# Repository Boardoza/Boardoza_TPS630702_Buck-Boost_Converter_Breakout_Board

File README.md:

# Boardoza TPS630702 Buck-Boost Regulator Module

The TPS630702 Buck-Boost Converter Breakout Board is an efficient, compact power management solution for applications requiring stable voltage output over a wide input voltage range. This module features automatic transition between step-down and boost mode, making it ideal for battery-powered projects. With high efficiency of up to 95%, adjustable output voltage selection, and multiple safety protections, it provides a reliable power supply for embedded systems, IoT devices, and other electronics requiring regulated power.

## [Click here to purchase!](https://www.ozdisan.com/maker-ve-iot-urunleri/boardoza/boardoza-modulleri/BOARDOZA-TPS630702/1206511)

|Front Side|Back Side|
|:---:|:---:|
| | |

---

## Key Features

- **Wide Input Voltage Range**: Operates from 2.0V to 16V, suitable for battery and adapter applications.
- **Selectable Output Voltage**: Provides 3.3V by default, with options for 5V, 7.5V, and 9V via jumper selection.
- **High Current Capability**: Supports up to **2A output in both Buck and Boost modes**.
- **Automatic Buck-Boost Transition**: Seamlessly switches between step-down and boost mode depending on input voltage.
- **Load Disconnect & Output Discharge**: Ensures safety during shutdown.
- **Efficiency**: Up to 95%, reducing heat dissipation and improving battery life.
- **Protection Features**: Includes input/output overvoltage protection and undervoltage lockout.

---

## Technical Specifications

**Input Voltage:** 2.0V - 16V  

**Input Voltage Type:** Molex 2-pin 2.50mm header  

**Functions:** Buck-Boost Voltage Regulator  

**Output Voltage:** 3.3V, 5V, 7.5V, 9V (Selectable)  

**Output Current:**

- **Buck Mode:** 2A
- **Boost Mode:** 2A (VIN = 4V, VOUT = 5V)  

**Efficiency:** Up to **95%**  

**Operating Temperature:** -40°C ~ +150°C  

**Board Dimensions:** 40mm x 60mm  

---

## **Board Pinout**

### **J1 - Power Input Connector**

| Pin Number | Pin Name | Description |
|:---:|:---:|---|
| 1 | VIN | Voltage Input Pin (2V - 16V) |
| 2 | GND | Ground |

### **J2 - Power Good (PG) Indicator**

| Pin Number | Pin Name | Description |
|:---:|:---:|---|
| 1 | PG | Power Good signal, indicating output voltage status. |
| 2 | GND | Ground |

### **J3 - Output Connector**

| Pin Number | Pin Name | Description |
|:---:|:---:|---|
| 1 | VOUT | Adjustable Buck-Boost output (3.3V - 5V - 7.5V - 9V) |
| 2 | GND | Ground |

### **JP1 - Enable Control**

| Pin Number | Pin Name | Description |
|:---:|:---:|---|
| 1 | LOW | Connect to GND |
| 2 | EN | Regulator Enable Pin (Default: HIGH). Set LOW to disable the regulator. |
| 3 | HIGH | Connect to VIN |

### **JP2 - Power Save / Synchronization Mode**

| Pin Number | Pin Name | Description |
|:---:|:---:|---|
| 1 | LOW | Open drain power good output |
| 2 | PS/SYNC | Selects between forced PWM and power-save mode. Default: LOW (PWM Mode). |
| 3 | HIGH | Connect to VIN |

### **JP3 - Voltage Selection**

| Pin Number | Pin Name | Description |
|:---:|:---:|---|
| 1 | LOW | Open drain power good output |
| 2 | V_SEL | Voltage selection input (Default: LOW for 3.3V). Set HIGH to select another voltage. |
| 3 | HIGH | Connect to VIN |

### **Voltage Selection Pads**

| Pad | Description |
|:---:|---|
| 9V | Select 9V output by jumping this pad |
| 7.5V | Select 7.5V output by jumping this pad |
| 5V | Select 5V output by jumping this pad |

---

## Board Dimensions

---

## Step Files

[Boardoza TPS63070.step](./assets/TPS630702%20Step.step)

---

## Datasheet

[Boardoza TPS63070 Datasheet.pdf](./assets/TPS630702%20Datasheet.pdf)

---

## Version History

- V1.0.0 - Initial Release

---

## Support

- If you have any questions or need support, please contact <support@boardoza.com>

---

## License

Shield: [![CC BY-SA 4.0][cc-by-sa-shield]][cc-by-sa]

This work is licensed under a [Creative Commons Attribution-ShareAlike 4.0 International License][cc-by-sa].

[![CC BY-SA 4.0][cc-by-sa-image]][cc-by-sa]

[cc-by-sa]: http://creativecommons.org/licenses/by-sa/4.0/
[cc-by-sa-image]: https://licensebuttons.net/l/by-sa/4.0/88x31.png
[cc-by-sa-shield]: https://img.shields.io/badge/License-CC%20BY--SA%204.0-lightgrey.svg

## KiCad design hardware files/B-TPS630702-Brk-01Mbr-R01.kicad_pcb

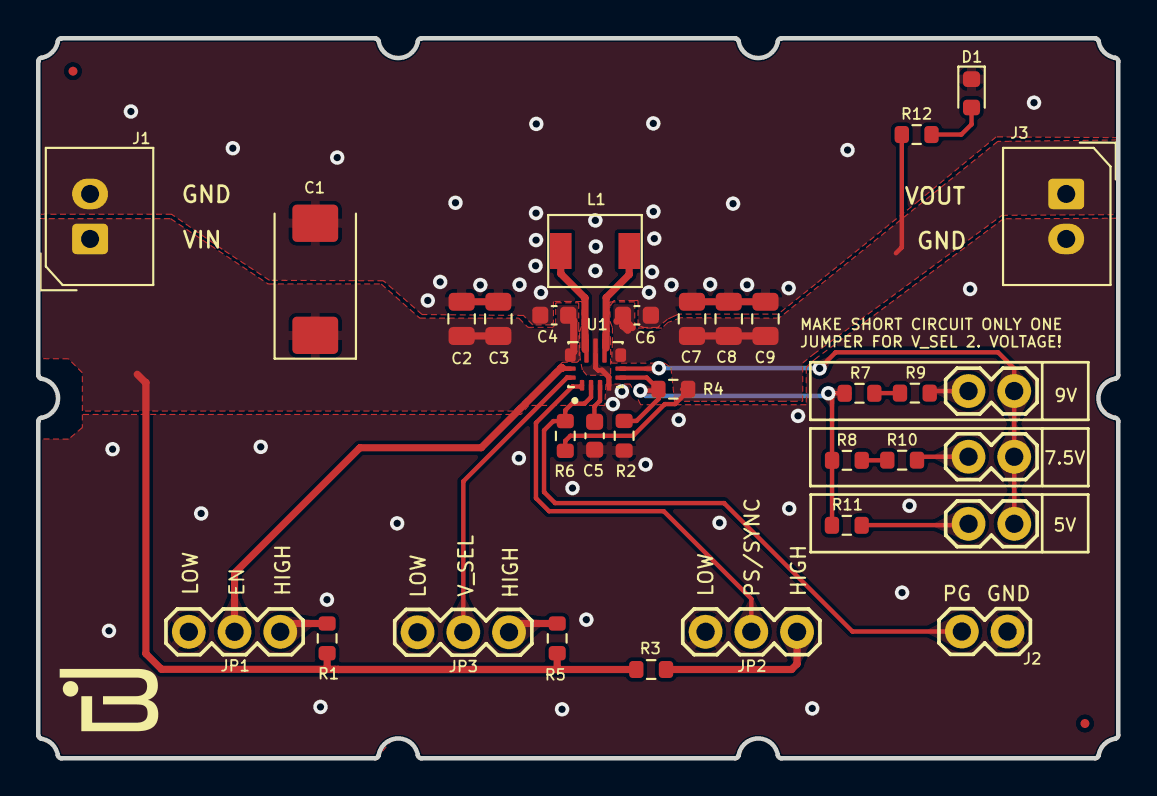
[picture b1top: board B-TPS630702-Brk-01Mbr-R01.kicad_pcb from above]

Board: 2 copper layers, 60.0 x 40.0 mm, 33 parts (0 on the bottom side), 21 nets.

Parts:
C1: 68uF; CP_EIA-7343-43_Kemet-X
C2, C3: 10uF; C_0805_2012Metric
C4, C6: 10uF; C_0603_1608Metric
C5: 100nF; C_0603_1608Metric
C7, C8, C9: 22uF; C_0805_2012Metric
D1: LED POWER; LED_0603_1608Metric
J1, J3: 2317-02; 2317-02S_1x02_P2.50mm_Vertical
J2: PG; 1X02
JP1: EN; 1X03
JP2: PS/SYNC; 1X03
JP3: VSEL; 1X03
JP4: 9V; 1X02
JP5: 5V; 1X02
JP6: 7.5V; 1X02
L1: SMPI04020-1R5M; SMPI04020
R1, R3, R5, R12: 10K; R_0603_1608Metric
R2: 150K; R_0603_1608Metric
R4: 470K; R_0603_1608Metric
R6: 100K; R_0603_1608Metric
R7: 51K; R_0603_1608Metric
R8: 71.5K; R_0603_1608Metric
R9: 15K; R_0603_1608Metric
R10: 18K; R_0603_1608Metric
R11: 221K; R_0603_1608Metric
U1: TPS630702RNMR; TPS63070RNMT

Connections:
+3V3: C6.1, C7.1, C8.1, C9.1, J3.1, R4.2, R6.1, R12.1, U1.7_8 (VOUT)
EN: JP1.2, U1.14 (EN)
FB: R2.2, R4.1, R7.1, R8.1, R11.1, U1.5 (FB)
FB2: JP4.2, JP5.2, JP6.2, U1.6 (FB2)
GND: C1.2, C2.2, C3.2, C4.2, C5.2, C6.2, C7.2, C8.2, C9.2, D1.1 (K), J1.2, J2.2, J3.2, JP1.1, JP2.1, JP3.1, R2.1, U1.4 (GND), U1.10 (PGND)
unnamed: D1.2 (A), R12.2
unnamed: JP1.3, R1.2
unnamed: JP2.3, R3.1
unnamed: JP3.3, R5.2
unnamed: JP4.1, R9.2
unnamed: JP5.1, R11.2
unnamed: JP6.1, R10.2
unnamed: R7.2, R9.1
unnamed: R8.2, R10.1
unnamed: L1.2, U1.11 (L1)
unnamed: L1.1, U1.9 (L2)
unnamed: C5.1, U1.3 (VAUX)
PG: J2.1, R6.2, U1.2 (PG)
PS/SYNC: JP2.2, U1.1 (PS/SYNC)
V_IN: C1.1, C2.1, C3.1, C4.1, J1.1, R1.1, R3.2, R5.1, U1.12_13 (VIN)
V_SEL: JP3.2, U1.15 (VSEL)

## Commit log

2024-09-03 Initial release for TPS630702 breakout board.
2024-09-03 Update image file names to match the correct part number
2025-03-19 Update README for TPS630702 module and replace image assets
